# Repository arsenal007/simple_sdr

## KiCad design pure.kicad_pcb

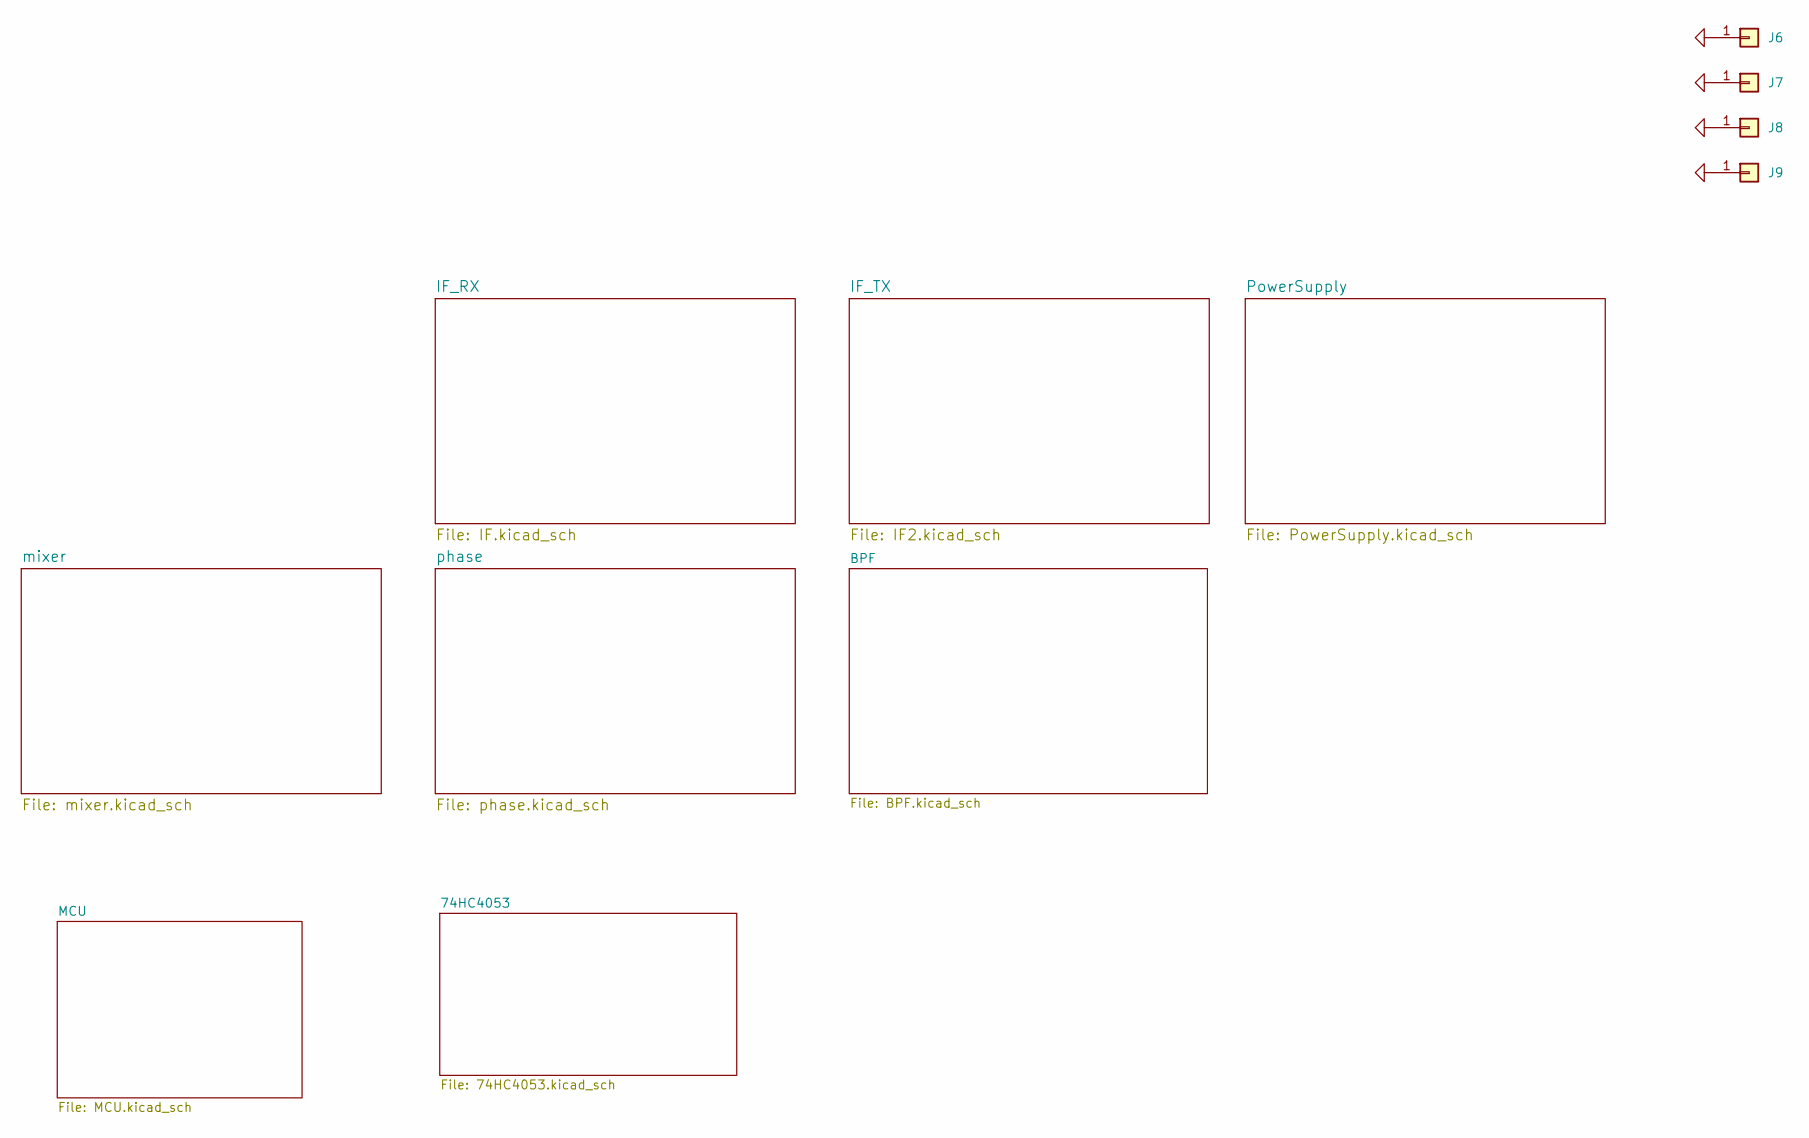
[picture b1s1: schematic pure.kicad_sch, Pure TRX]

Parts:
J6, J7, J8, J9: Conn_01x01; MountingHole_3.2mm_M3_DIN965_Pad

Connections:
GND: J6.1, J7.1, J8.1, J9.1; also elsewhere on the board

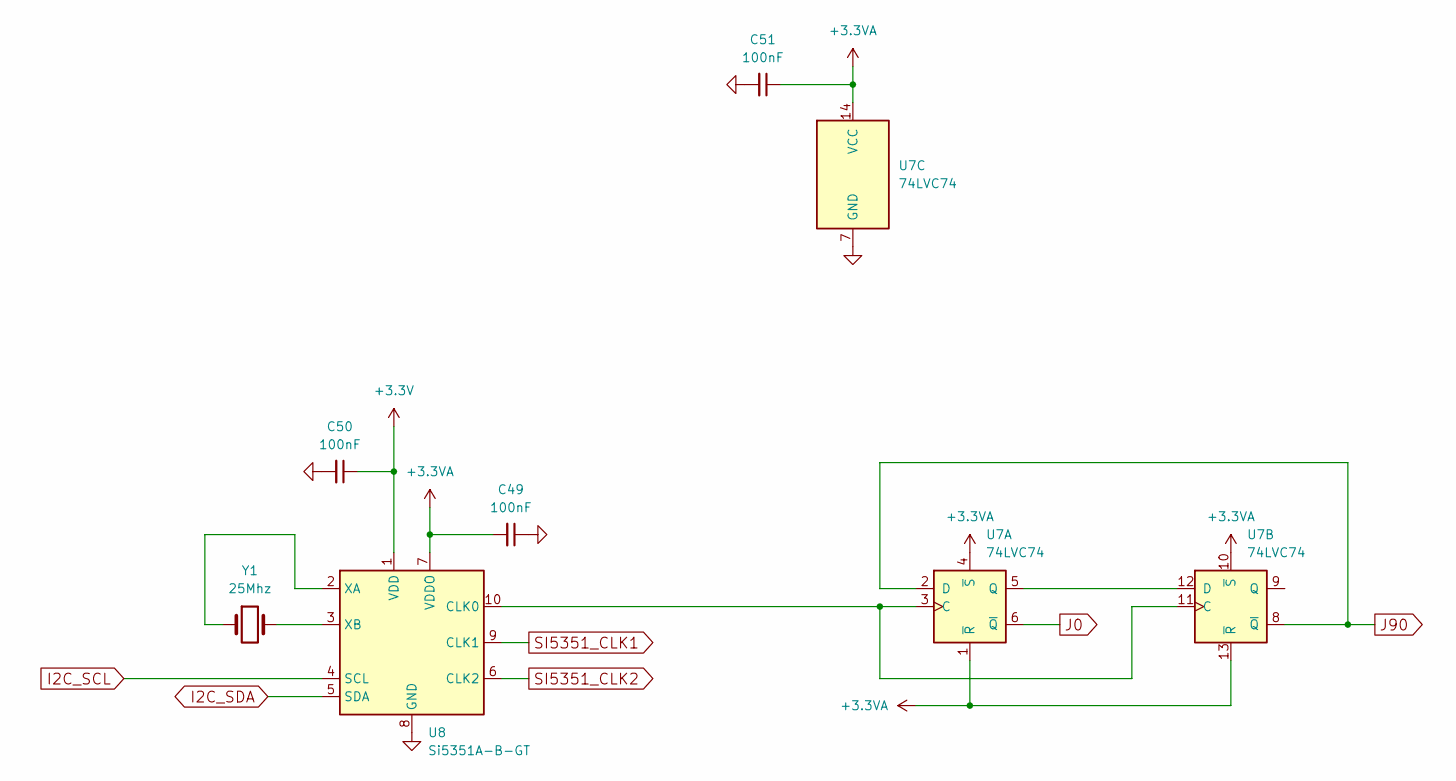
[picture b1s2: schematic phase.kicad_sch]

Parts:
C49, C50, C51: 100nF; C_1206_0603
U7: 74LVC74; TSSOP-14_4.4x5mm_P0.65mm
U8: Si5351A-B-GT; MSOP-10_3x3mm_P0.5mm
Y1: 25Mhz; Crystal_HC49-U_Vertical

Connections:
+3.3V: C50.1, U8.1 (VDD); also elsewhere on the board
+3.3VA: C49.2, C51.1, U7.1 (~R), U7.4 (~S), U7.10 (~S), U7.13 (~R), U7.14 (VCC), U8.7 (VDDO); also elsewhere on the board
GND: C49.1, C50.2, C51.2, U7.7 (GND), U8.8 (GND); also elsewhere on the board
I2C_SCL: U8.4 (SCL); also elsewhere on the board
I2C_SDA: U8.5 (SDA); also elsewhere on the board
J0: U7.6 (~Q); also elsewhere on the board
J90: U7.2 (D), U7.8 (~Q); also elsewhere on the board
unnamed: U7.3 (C), U7.11 (C), U8.10 (CLK0)
unnamed: U7.5 (Q), U7.12 (D)
unnamed: U8.2 (XA), Y1.1
unnamed: U8.3 (XB), Y1.2
SI5351_CLK1: U8.9 (CLK1)
SI5351_CLK2: U8.6 (CLK2)

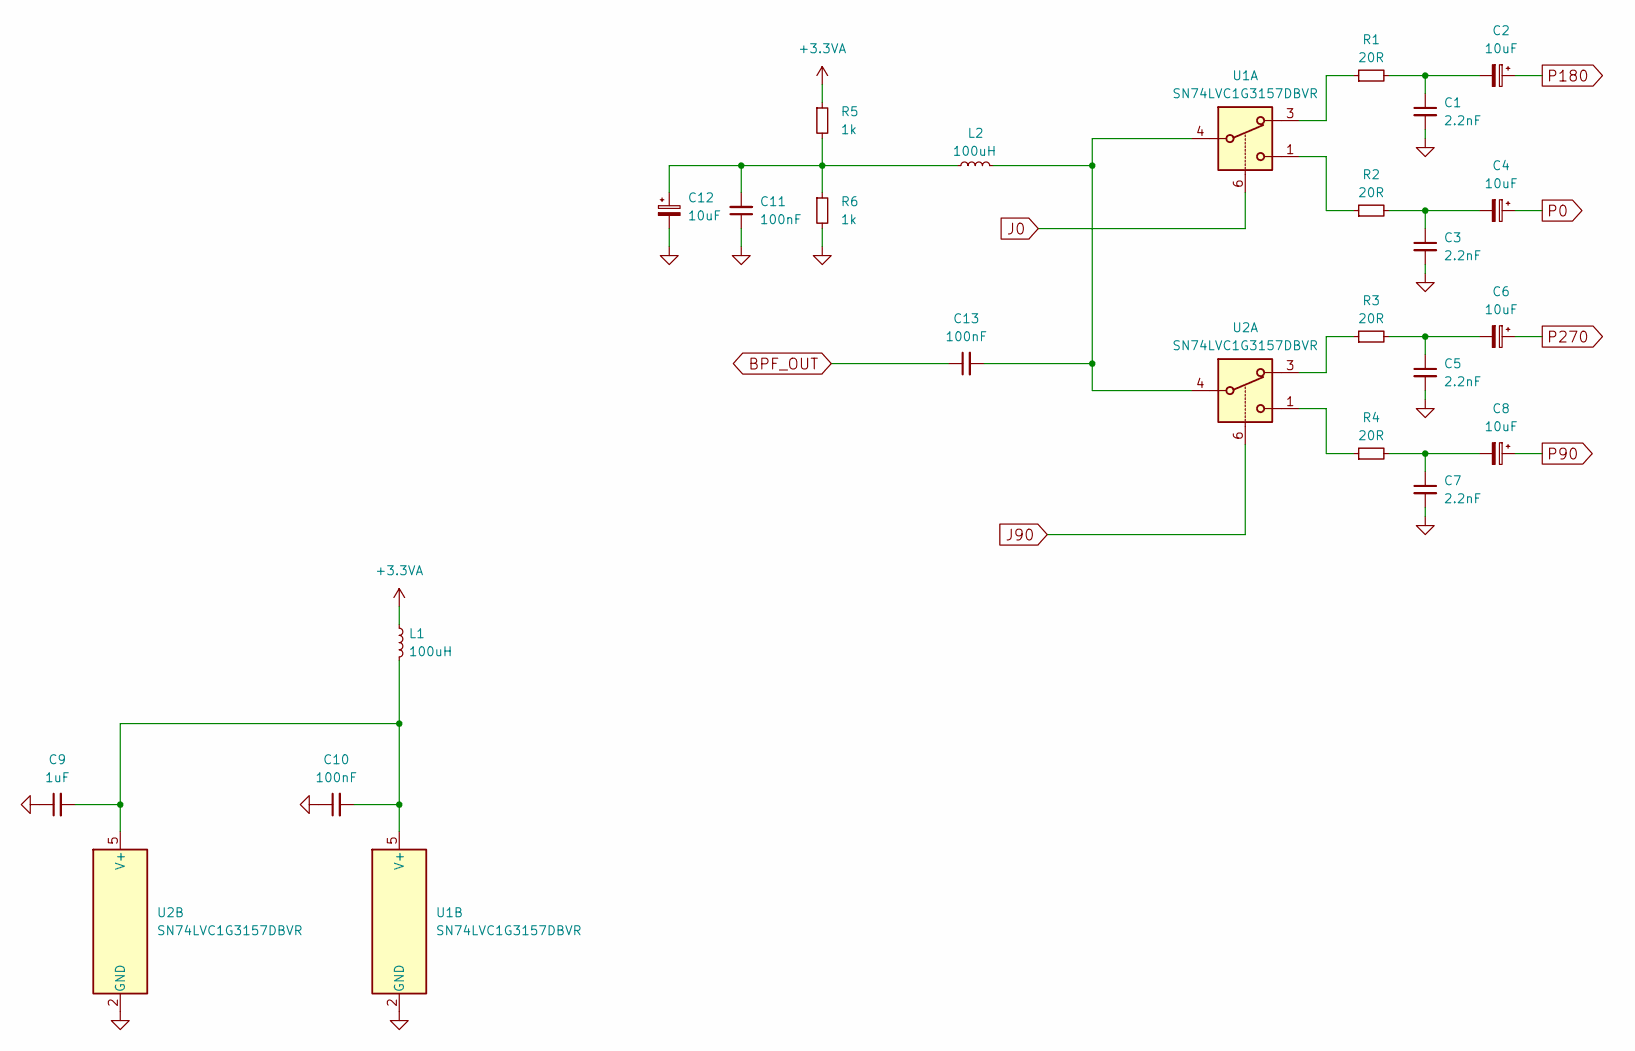
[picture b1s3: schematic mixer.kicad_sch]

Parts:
C1, C3, C5, C7: 2.2nF; C_1206_0603; JLCPCB C1604
C2, C4, C6, C8, C12: 10uF; CP_EIA-3216-18_Kemet-A_Pad1.58x1.35mm_HandSolder; JLCPCB C123294
C9: 1uF; C_0603_1608Metric_Pad1.08x0.95mm_HandSolder; JLCPCB C15849
C10, C11: 100nF; C_0603_1608Metric_Pad1.08x0.95mm_HandSolder; JLCPCB C14663
C13: 100nF; C_1206_0603; JLCPCB C14663
L1, L2: 100uH; L_Axial_L5.3mm_D2.2mm_P10.16mm_Horizontal_Vishay_IM-1; JLCPCB C394100
R1, R2, R3, R4: 20R; R_1206_0603; JLCPCB C22950
R5, R6: 1k; R_0603_1608Metric_Pad0.98x0.95mm_HandSolder; JLCPCB C21190
U1, U2: SN74LVC1G3157DBVR; SOT-23-6; JLCPCB C10426

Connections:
+3.3VA: L1.1, R5.1; also elsewhere on the board
BPF_OUT: C13.1; also elsewhere on the board
GND: C1.2, C3.2, C5.2, C7.2, C9.1, C10.1, C11.1, C12.2, R6.2, U1.2 (GND), U2.2 (GND); also elsewhere on the board
J0: U1.6; also elsewhere on the board
J90: U2.6; also elsewhere on the board
unnamed: C1.1, C2.2, R1.2
unnamed: C3.1, C4.2, R2.2
unnamed: C5.1, C6.2, R3.2
unnamed: C7.1, C8.2, R4.2
unnamed: C11.2, C12.1, L2.1, R5.2, R6.1
unnamed: C13.2, L2.2, U1.4, U2.4
unnamed: R1.1, U1.3
unnamed: R2.1, U1.1
unnamed: R3.1, U2.3
unnamed: R4.1, U2.1
unnamed: C9.2, C10.2, L1.2, U1.5 (V+), U2.5 (V+)
P0: C4.1; also elsewhere on the board
P90: C8.1; also elsewhere on the board
P180: C2.1; also elsewhere on the board
P270: C6.1; also elsewhere on the board

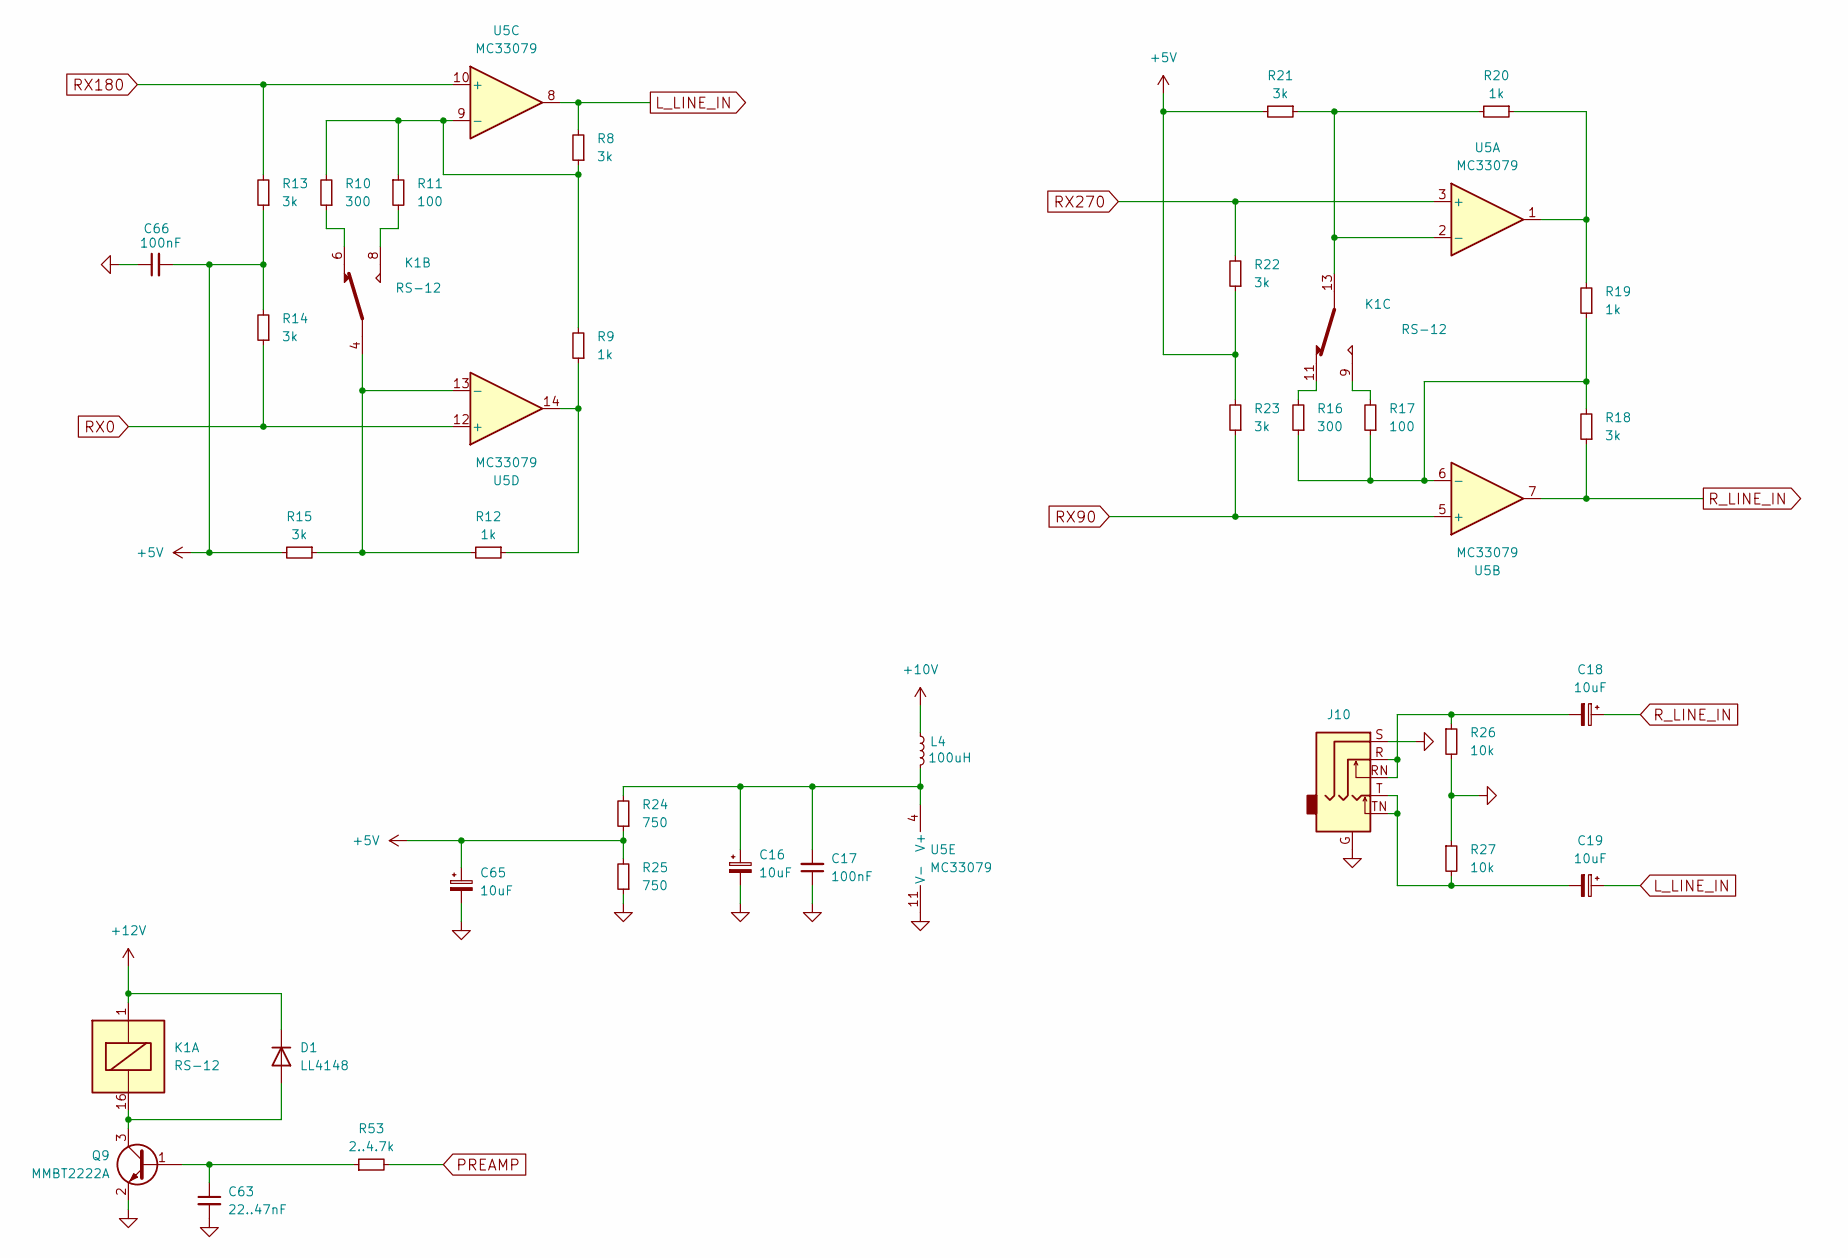
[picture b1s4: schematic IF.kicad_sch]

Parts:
C16, C18, C19, C65: 10uF; CP_EIA-3216-18_Kemet-A_Pad1.58x1.35mm_HandSolder; JLCPCB C123294
C17, C66: 100nF; C_1206_0603; JLCPCB C14663
C63: 22..47nF; C_1206_0603
D1: LL4148; D_MiniMELF
J10: AudioJack3_Ground_SwitchTR; Jack_3.5mm_CUI_SJ1-3525N_Horizontal
K1: RS-12; Relay_DPDT_Omron_G5V-2
L4: 100uH; L_1210_3225Metric_Pad1.42x2.65mm_HandSolder; JLCPCB C394100
Q9: MMBT2222A; SOT-23
R8, R13, R14, R15, R18, R21, R22, R23: 3k; R_0603_1608Metric_Pad0.98x0.95mm_HandSolder; JLCPCB C4211
R9, R12, R19, R20: 1k; R_0603_1608Metric_Pad0.98x0.95mm_HandSolder; JLCPCB C21190
R10, R16: 300; R_0603_1608Metric_Pad0.98x0.95mm_HandSolder; JLCPCB C23025
R11, R17: 100; R_0603_1608Metric_Pad0.98x0.95mm_HandSolder; JLCPCB C22775
R24, R25: 750; R_1206_0603; JLCPCB C23241
R26, R27: 10k; R_0603_1608Metric_Pad0.98x0.95mm_HandSolder; JLCPCB C25804
R53: 2..4.7k; R_1206_0603
U5: MC33079; SOIC-14_3.9x8.7mm_P1.27mm

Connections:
+5V: C65.1, C66.2, R13.1, R14.2, R15.2, R21.2, R22.1, R23.2, R24.1, R25.2; also elsewhere on the board
+10V: L4.1; also elsewhere on the board
+12V: D1.1 (K), K1.1; also elsewhere on the board
GND: C16.2, C17.1, C63.2, C65.2, C66.1, J10.G, J10.S, Q9.2 (E), R25.1, R26.2, R27.1, U5.11 (V-); also elsewhere on the board
L_LINE_IN: C19.1, R8.2, U5.8
unnamed: C18.2, J10.R, J10.RN, R26.1
unnamed: C19.2, J10.T, J10.TN, R27.2
unnamed: D1.2 (A), K1.16, Q9.3 (C)
unnamed: K1.6, R10.1
unnamed: K1.8, R11.2
unnamed: K1.9, R17.2
unnamed: K1.11, R16.2
unnamed: C63.1, Q9.1 (B), R53.1
unnamed: R9.1, R12.1, U5.14
unnamed: R19.2, R20.1, U5.1
unnamed: K1.13, R20.2, R21.1, U5.2 (-)
unnamed: R16.1, R17.1, R18.2, R19.1, U5.6 (-)
unnamed: R8.1, R9.2, R10.2, R11.1, U5.9 (-)
unnamed: K1.4, R12.2, R15.1, U5.13 (-)
unnamed: C16.1, C17.2, L4.2, R24.2, U5.4 (V+)
PREAMP: R53.2; also elsewhere on the board
RX0: R14.1, U5.12 (+); also elsewhere on the board
RX90: R23.1, U5.5 (+); also elsewhere on the board
RX180: R13.2, U5.10 (+); also elsewhere on the board
RX270: R22.2, U5.3 (+); also elsewhere on the board
R_LINE_IN: C18.1, R18.1, U5.7

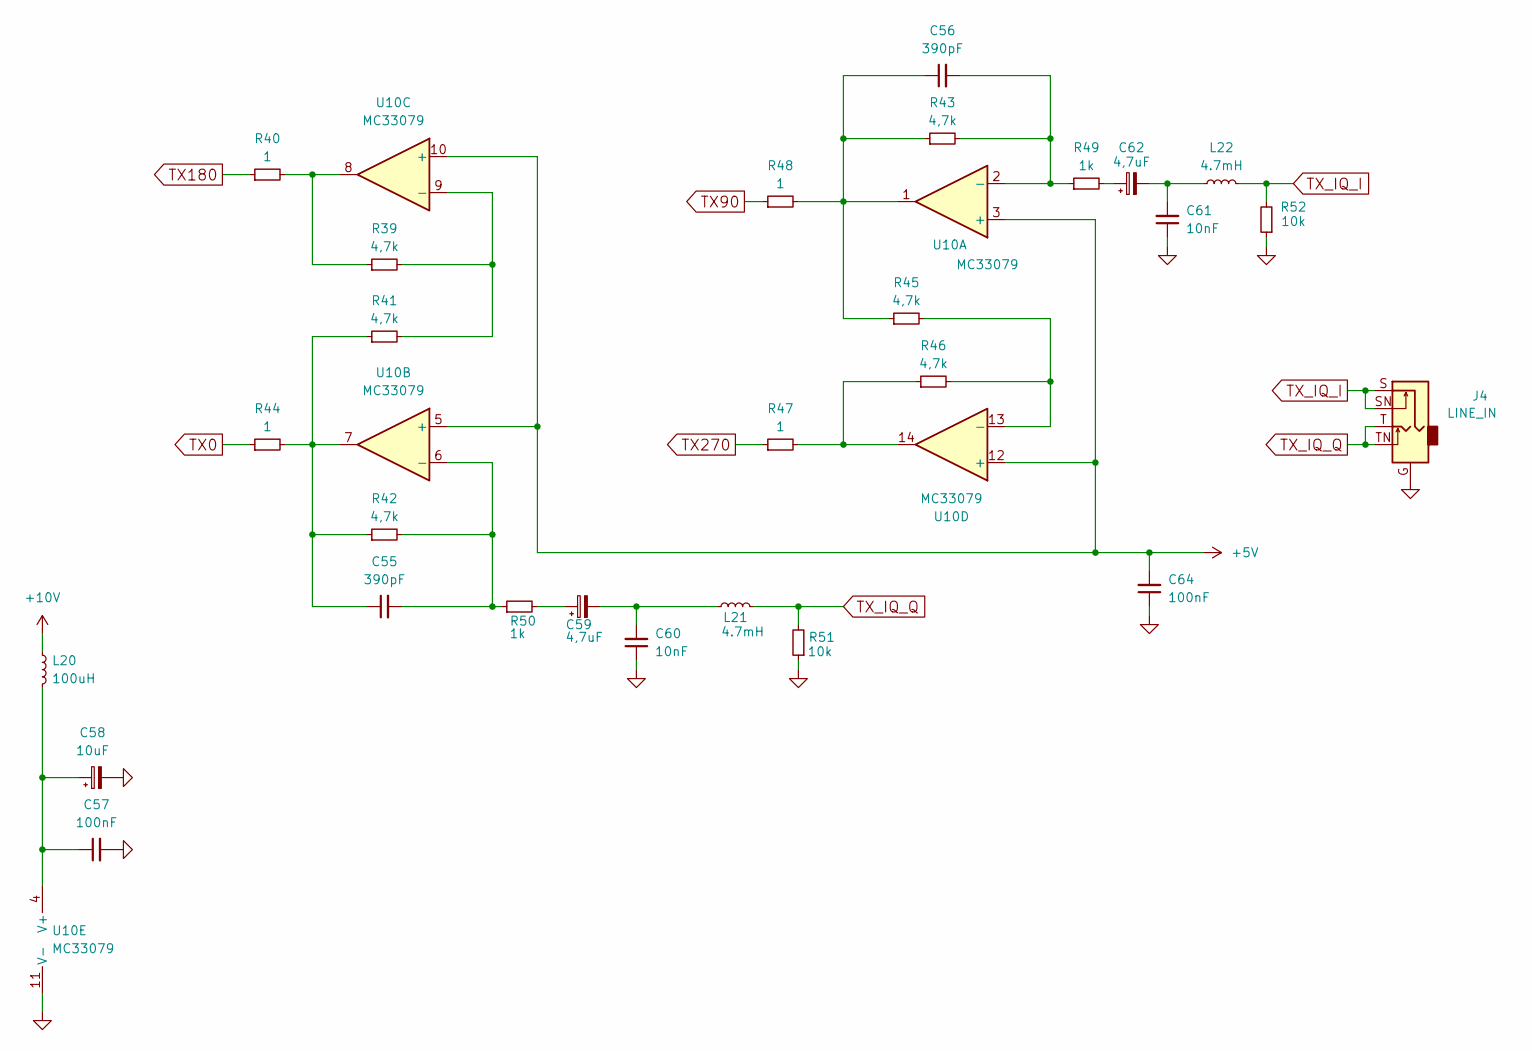
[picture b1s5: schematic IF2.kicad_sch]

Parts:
C55, C56: 390pF; C_0603_1608Metric_Pad1.08x0.95mm_HandSolder
C57: 100nF
C58: 10uF
C59, C62: 4,7uF
C60, C61: 10nF
C64: 100nF; C_1206_0603
J4: LINE_IN; Jack_3.5mm_CUI_SJ1-3525N_Horizontal
L20: 100uH
L21, L22: 4.7mH
R39, R41, R42, R43, R45, R46: 4,7k; R_0603_1608Metric_Pad0.98x0.95mm_HandSolder
R40, R44, R47, R48: 1; R_1206_0603
R49, R50: 1k; R_0603_1608Metric_Pad0.98x0.95mm_HandSolder
R51, R52: 10k
U10: MC33079; SOIC-14_3.9x8.7mm_P1.27mm

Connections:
+5V: C64.2, U10.3 (+), U10.5 (+), U10.10 (+), U10.12 (+); also elsewhere on the board
GND: C57.2, C58.2, C60.1, C61.1, C64.1, J4.G, R51.1, R52.1, U10.11 (V-); also elsewhere on the board
unnamed: C55.1, R41.1, R42.1, R44.2, U10.7
unnamed: C56.1, R43.1, R45.1, R48.2, U10.1
unnamed: C59.1, R50.2
unnamed: C59.2, C60.2, L21.1
unnamed: C61.2, C62.2, L22.1
unnamed: C62.1, R49.2
unnamed: R39.1, R40.2, U10.8
unnamed: R46.1, R47.2, U10.14
unnamed: C56.2, R43.2, R49.1, U10.2 (-)
unnamed: C55.2, R42.2, R50.1, U10.6 (-)
unnamed: R39.2, R41.2, U10.9 (-)
unnamed: R45.2, R46.2, U10.13 (-)
unnamed: C57.1, C58.1, L20.2, U10.4 (V+)
TX0: R44.1; also elsewhere on the board
TX90: R48.1; also elsewhere on the board
TX180: R40.1; also elsewhere on the board
TX270: R47.1; also elsewhere on the board
TX_IQ_I: J4.S, J4.SN, L22.2, R52.2
TX_IQ_Q: J4.T, J4.TN, L21.2, R51.2

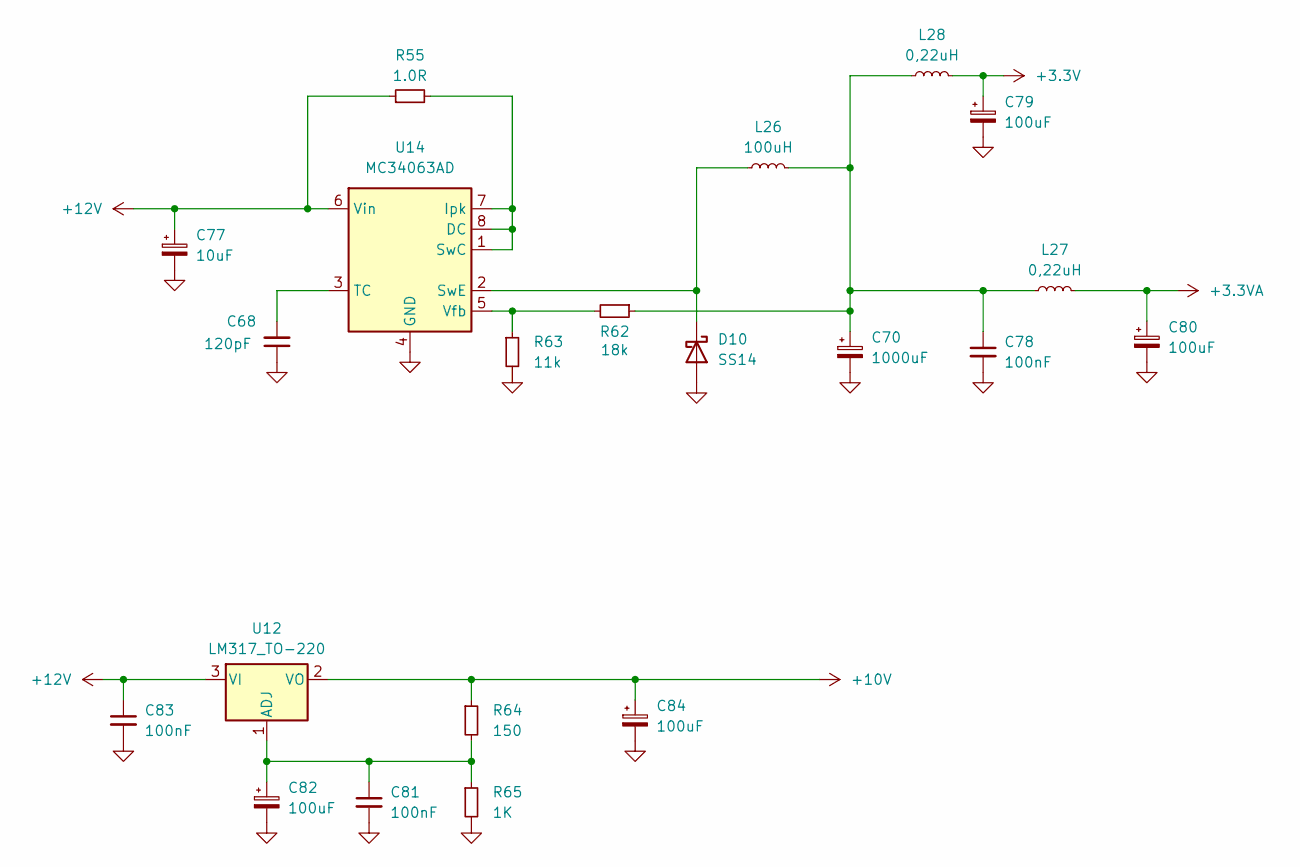
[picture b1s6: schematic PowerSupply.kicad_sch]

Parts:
C68: 120pF; C_0603_1608Metric_Pad1.08x0.95mm_HandSolder
C70: 1000uF
C77: 10uF; CP_Radial_D5.0mm_P2.00mm
C78, C81, C83: 100nF; C_1206_0603
C79, C80, C82, C84: 100uF; CP_Radial_D6.3mm_P2.50mm
D10: SS14; D_SMA
L26: 100uH
L27, L28: 0,22uH; R_Axial_DIN0207_L6.3mm_D2.5mm_P10.16mm_Horizontal
R55: 1.0R; R_1206_0603
R62: 18k; R_1206_0603
R63: 11k; R_1206_0603
R64: 150; R_1206_0603
R65: 1K; R_1206_0603
U12: LM317_TO-220; TO-220-3_Horizontal_TabDown
U14: MC34063AD; SOIC-8_3.9x4.9mm_P1.27mm

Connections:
+3.3V: C79.1, L28.2; also elsewhere on the board
+3.3VA: C80.1, L27.2; also elsewhere on the board
+10V: C84.1, R64.1, U12.2 (VO); also elsewhere on the board
+12V: C77.1, C83.1, R55.1, U12.3 (VI), U14.6 (Vin); also elsewhere on the board
GND: C68.1, C70.2, C77.2, C78.2, C79.2, C80.2, C81.2, C82.2, C83.2, C84.2, D10.2 (A), R63.2, R65.2, U14.4 (GND); also elsewhere on the board
unnamed: C70.1, C78.1, L26.2, L27.1, L28.1, R62.1
unnamed: D10.1 (K), L26.1, U14.2 (SwE)
unnamed: C81.1, C82.1, R64.2, R65.1, U12.1 (ADJ)
unnamed: R55.2, U14.1 (SwC), U14.7 (Ipk), U14.8 (DC)
unnamed: C68.2, U14.3 (TC)
unnamed: R62.2, R63.1, U14.5 (Vfb)

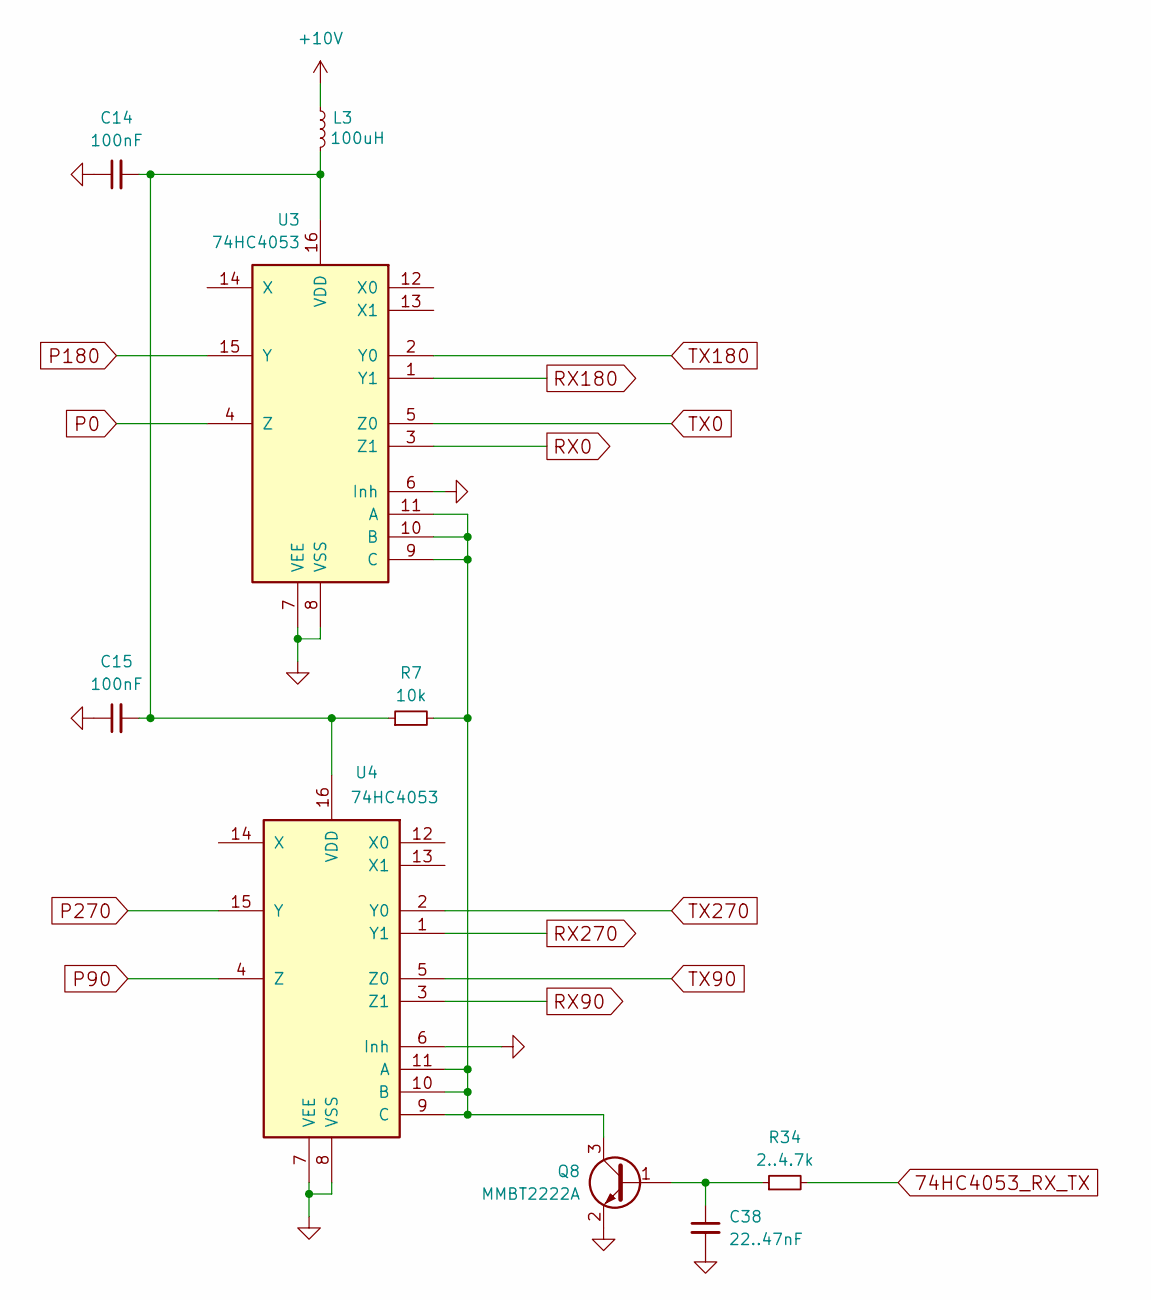
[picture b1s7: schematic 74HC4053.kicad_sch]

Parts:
C14, C15: 100nF; C_0603_1608Metric_Pad1.08x0.95mm_HandSolder; JLCPCB C14663
C38: 22..47nF
L3: 100uH; L_1210_3225Metric_Pad1.42x2.65mm_HandSolder; JLCPCB C394100
Q8: MMBT2222A; SOT-23
R7: 10k; R_0603_1608Metric_Pad0.98x0.95mm_HandSolder; JLCPCB C25804
R34: 2..4.7k
U3, U4: 74HC4053; SO-16_3.9x9.9mm_P1.27mm; JLCPCB C9386

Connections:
+10V: L3.1; also elsewhere on the board
GND: C14.1, C15.1, C38.2, Q8.2 (E), U3.6 (Inh), U3.7 (VEE), U3.8 (VSS), U4.6 (Inh), U4.7 (VEE), U4.8 (VSS); also elsewhere on the board
unnamed: C38.1, Q8.1 (B), R34.1
unnamed: Q8.3 (C), R7.2, U3.9 (C), U3.10 (B), U3.11 (A), U4.9 (C), U4.10 (B), U4.11 (A)
unnamed: C14.2, C15.2, L3.2, R7.1, U3.16 (VDD), U4.16 (VDD)
P0: U3.4 (Z); also elsewhere on the board
P90: U4.4 (Z); also elsewhere on the board
P180: U3.15 (Y); also elsewhere on the board
P270: U4.15 (Y); also elsewhere on the board
RX0: U3.3 (Z1); also elsewhere on the board
RX90: U4.3 (Z1); also elsewhere on the board
RX180: U3.1 (Y1); also elsewhere on the board
RX270: U4.1 (Y1); also elsewhere on the board
TX0: U3.5 (Z0); also elsewhere on the board
TX90: U4.5 (Z0); also elsewhere on the board
TX180: U3.2 (Y0); also elsewhere on the board
TX270: U4.2 (Y0); also elsewhere on the board

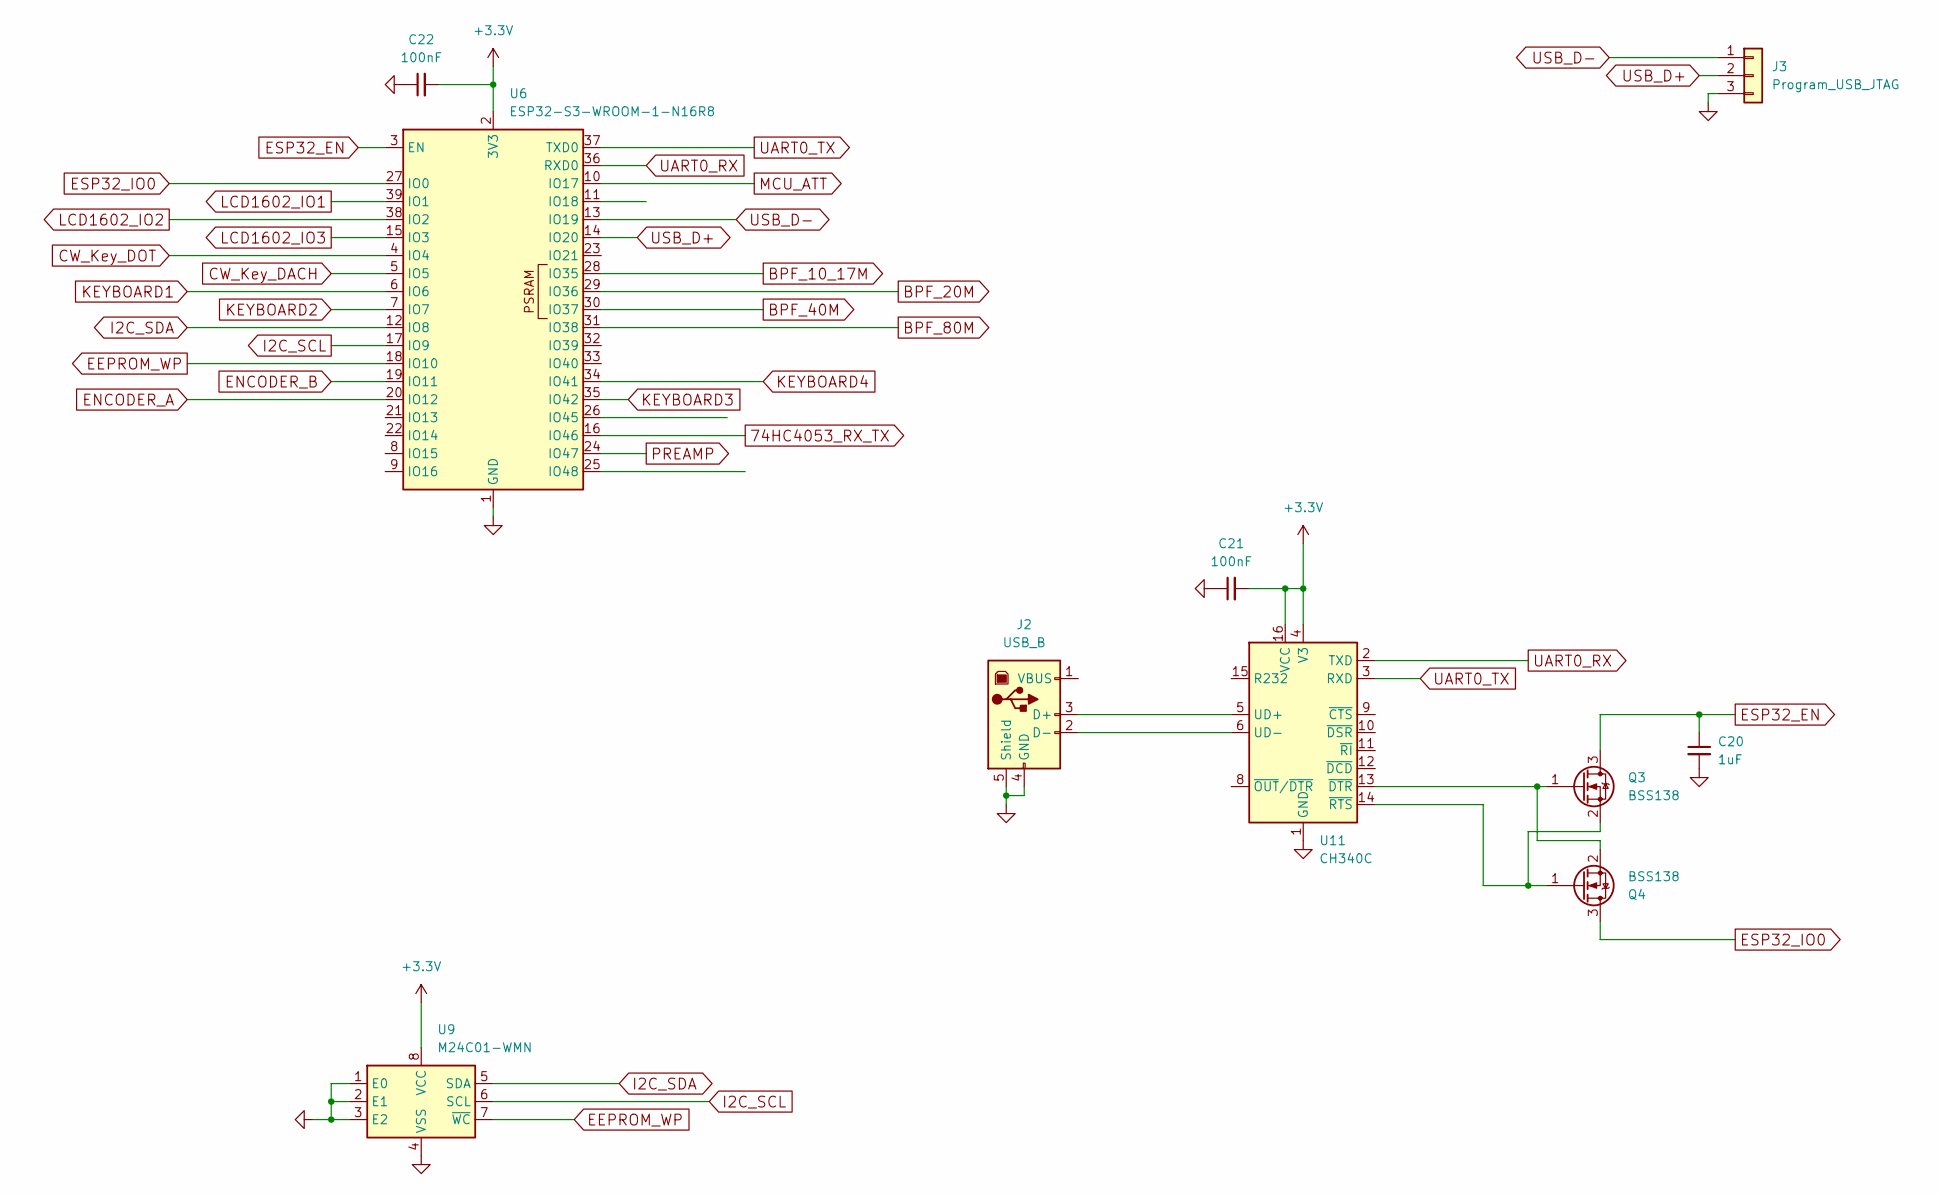
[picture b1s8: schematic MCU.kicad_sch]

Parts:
C20: 1uF; C_0603_1608Metric_Pad1.08x0.95mm_HandSolder; JLCPCB C15849
C21, C22: 100nF; C_0603_1608Metric_Pad1.08x0.95mm_HandSolder; JLCPCB C14663
J2: USB_B; USB_B_OST_USB-B1HSxx_Horizontal
J3: Program_USB_JTAG; PinHeader_1x03_P2.54mm_Vertical
Q3: BSS138; SOT-23; JLCPCB C82045
Q4: BSS138; SOT-23
U6: ESP32-S3-WROOM-1-N16R8; ESP32-S3-WROOM-1; JLCPCB C2913202
U9: M24C01-WMN; SOIC-8_3.9x4.9mm_P1.27mm
U11: CH340C; SOIC-16_3.9x9.9mm_P1.27mm; JLCPCB C7464026

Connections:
74HC4053_RX_TX: U6.16 (IO46)
+3.3V: C21.2, C22.2, U6.2 (3V3), U9.8 (VCC), U11.4 (V3), U11.16 (VCC); also elsewhere on the board
BPF_10_17M: U6.28 (IO35); also elsewhere on the board
BPF_20M: U6.29 (IO36); also elsewhere on the board
BPF_40M: U6.30 (IO37); also elsewhere on the board
BPF_80M: U6.31 (IO38); also elsewhere on the board
CW_Key_DACH: U6.5 (IO5)
CW_Key_DOT: U6.4 (IO4)
EEPROM_WP: U6.18 (IO10), U9.7 (~WC)
ENCODER_A: U6.20 (IO12)
ENCODER_B: U6.19 (IO11)
ESP32_EN: C20.1, Q3.3 (D), U6.3 (EN)
ESP32_IO0: Q4.3 (D), U6.27 (IO0)
GND: C20.2, C21.1, C22.1, J2.4 (GND), J2.5 (Shield), J3.3, U6.1 (GND), U6.40 (GND), U6.41 (GND), U9.1 (E0), U9.2 (E1), U9.3 (E2), U9.4 (VSS), U11.1 (GND); also elsewhere on the board
I2C_SCL: U6.17 (IO9), U9.6 (SCL); also elsewhere on the board
I2C_SDA: U6.12 (IO8), U9.5 (SDA); also elsewhere on the board
KEYBOARD1: U6.6 (IO6)
KEYBOARD2: U6.7 (IO7)
KEYBOARD3: U6.35 (IO42)
KEYBOARD4: U6.34 (IO41)
LCD1602_IO1: U6.39 (IO1)
LCD1602_IO2: U6.38 (IO2)
LCD1602_IO3: U6.15 (IO3)
MCU_ATT: U6.10 (IO17); also elsewhere on the board
unnamed: J2.3 (D+), U11.5 (UD+)
unnamed: J2.2 (D-), U11.6 (UD-)
unnamed: Q3.1 (G), Q4.2 (S), U11.13 (~DTR)
unnamed: Q3.2 (S), Q4.1 (G), U11.14 (~RTS)
PREAMP: U6.24 (IO47); also elsewhere on the board
UART0_RX: U6.36 (RXD0), U11.2 (TXD)
UART0_TX: U6.37 (TXD0), U11.3 (RXD)
USB_D+: J3.2, U6.14 (IO20)
USB_D-: J3.1, U6.13 (IO19)

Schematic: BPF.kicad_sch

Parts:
C52, C53: 100nF; C_1206_0603
C54: 10uF; CP_EIA-3216-18_Kemet-A_Pad1.58x1.35mm_HandSolder
L17: 10uH
L18, L19: 100uH; L_Axial_L5.3mm_D2.2mm_P10.16mm_Horizontal_Vishay_IM-1
R37, R38: 1k; R_0603_1608Metric_Pad0.98x0.95mm_HandSolder

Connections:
12v_BPF: C52.1, C53.1, C54.1, L17.2, L18.1, L19.1; also elsewhere on the board
BPF_IN: R38.2; also elsewhere on the board
BPF_OUT: R37.2; also elsewhere on the board
GND: C52.2, C53.2, C54.2; also elsewhere on the board
unnamed: L18.2, R37.1
unnamed: L19.2, R38.1

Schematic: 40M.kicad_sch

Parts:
C33: 360; C_0603_1608Metric_Pad1.08x0.95mm_HandSolder; JLCPCB C694496
C34: 390; C_0603_1608Metric_Pad1.08x0.95mm_HandSolder; JLCPCB C599667
C35: 100nF; C_1206_0603
C36: 360; C_1206_0603; JLCPCB C694496
C37: 22..47nF; C_1206_0603
C39: 470; C_0603_1608Metric_Pad1.08x0.95mm_HandSolder; JLCPCB C694496
C40: 470; C_1206_0603; JLCPCB C694496
D6, D7: BAP50-03; D_SOD-323_HandSoldering; JLCPCB C130411
L11, L13: 1uH; Resistor_SMD+THTuniversal_0603to2512_RM10_HandSoldering
L12: 2,2uH; Resistor_SMD+THTuniversal_0603to2512_RM10_HandSoldering
Q7: MMBT2222A; SOT-23
R32: 10k; R_0603_1608Metric_Pad0.98x0.95mm_HandSolder; JLCPCB C25804
R33: 2..4.7k; R_1206_0603

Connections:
12v_BPF: R32.1; also elsewhere on the board
BPF_40M: R33.2; also elsewhere on the board
BPF_IN: D6.2 (A); also elsewhere on the board
BPF_OUT: D7.2 (A); also elsewhere on the board
GND: C33.2, C35.2, C36.2, C37.2, C39.2, C40.2, Q7.2 (E); also elsewhere on the board
unnamed: C34.2, L12.1
unnamed: C33.1, C34.1, C39.1, D6.1 (K), L11.1
unnamed: C36.1, C40.1, D7.1 (K), L12.2, L13.1
unnamed: C37.1, Q7.1 (B), R33.1
unnamed: C35.1, L11.2, L13.2, Q7.3 (C), R32.2

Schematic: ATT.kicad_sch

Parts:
C67, C71: 100nF; C_1206_0603
C69: 22..47nF; C_1206_0603
C72: 120pF; C_0603_1608Metric_Pad1.08x0.95mm_HandSolder
C73: 220pF; C_1206_0603
C74: 120pF
C75, C76: 3,3nF; C_1206_0603
D11: LL4148; D_MiniMELF
J5: INPUT_OUTPUT; U.FL_Molex_MCRF_73412-0110_Vertical
K2: RS-12; Relay_DPDT_Omron_G5V-2
L23, L24: 0,22uH; Resistor_SMD+THTuniversal_0603to2512_RM10_HandSoldering
L25: 4,7uH; Resistor_SMD+THTuniversal_0603to2512_RM10_HandSoldering
Q2: MMBT2222A; SOT-23
R54: 2..4.7k; R_1206_0603
R56, R57, R58, R59, R60, R61: 1k; R_1206_0603

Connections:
+12V: D11.1 (K), K2.1; also elsewhere on the board
BPF_IN: C67.1; also elsewhere on the board
GND: C69.2, C72.1, C73.1, C74.1, J5.2 (Ext), L25.1, Q2.2 (E), R56.1, R58.1, R59.1, R61.1; also elsewhere on the board
MCU_ATT: R54.2; also elsewhere on the board
unnamed: C67.2, K2.13
unnamed: C71.1, C74.2, L23.2
unnamed: C71.2, K2.4
unnamed: C72.2, C75.1, L24.1
unnamed: C73.2, L23.1, L24.2
unnamed: C75.2, C76.1, L25.2
unnamed: D11.2 (A), K2.16, Q2.3 (C)
unnamed: C76.2, J5.1 (In)
unnamed: K2.8, R57.1, R58.2, R59.2, R60.1
unnamed: K2.9, R56.2, R57.2, R60.2, R61.2
unnamed: K2.6, K2.11
unnamed: C69.1, Q2.1 (B), R54.1

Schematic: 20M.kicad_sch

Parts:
C27, C29: 390; C_1206_0603; JLCPCB C694496
C28: 180; C_1206_0603; JLCPCB C599667
C30: 22..47nF; C_1206_0603
C31: 100nF; C_1206_0603
D4, D5: BAP50-03; D_SOD-323_HandSoldering; JLCPCB C130411
L8, L10: 0,47uH; Resistor_SMD+THTuniversal_0603to2512_RM10_HandSoldering
L9: 1uH; Resistor_SMD+THTuniversal_0603to2512_RM10_HandSoldering
Q5: MMBT2222A; SOT-23
R30: 10k; R_0603_1608Metric_Pad0.98x0.95mm_HandSolder; JLCPCB C25804
R31: 2..4.7k; R_1206_0603

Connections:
12v_BPF: R30.1; also elsewhere on the board
BPF_20M: R31.2; also elsewhere on the board
BPF_IN: D4.2 (A); also elsewhere on the board
BPF_OUT: D5.2 (A); also elsewhere on the board
GND: C27.2, C29.2, C30.2, C31.2, Q5.2 (E); also elsewhere on the board
unnamed: C28.2, L9.1
unnamed: C27.1, C28.1, D4.1 (K), L8.1
unnamed: C29.1, D5.1 (K), L9.2, L10.1
unnamed: C30.1, Q5.1 (B), R31.1
unnamed: C31.1, L8.2, L10.2, Q5.3 (C), R30.2

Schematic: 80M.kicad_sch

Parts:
C41, C45: 1nF; C_0603_1608Metric_Pad1.08x0.95mm_HandSolder; JLCPCB C694496
C42, C46: 560; C_0603_1608Metric_Pad1.08x0.95mm_HandSolder; JLCPCB C694496
C43: 120; C_0603_1608Metric_Pad1.08x0.95mm_HandSolder; JLCPCB C599667
C44: 100nF; C_1206_0603
C47: 22..47nF; C_1206_0603
C48: 560; C_0603_1608Metric_Pad1.08x0.95mm_HandSolder; JLCPCB C599667
D8, D9: BAP50-03; D_SOD-323_HandSoldering; JLCPCB C130411
L14, L16: 2,2uH; Resistor_SMD+THTuniversal_0603to2512_RM10_HandSoldering
L15: 4,7uH; Resistor_SMD+THTuniversal_0603to2512_RM10_HandSoldering
Q1: MMBT2222A; SOT-23
R35: 10k; R_0603_1608Metric_Pad0.98x0.95mm_HandSolder; JLCPCB C25804
R36: 2..4.7k; R_1206_0603

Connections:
12v_BPF: R35.1; also elsewhere on the board
BPF_80M: R36.2; also elsewhere on the board
BPF_IN: D8.2 (A); also elsewhere on the board
BPF_OUT: D9.2 (A); also elsewhere on the board
GND: C41.2, C42.2, C44.2, C45.2, C46.2, C47.2, Q1.2 (E); also elsewhere on the board
unnamed: C43.2, C48.2, L15.1
unnamed: C41.1, C42.1, C43.1, C48.1, D8.1 (K), L14.1
unnamed: C45.1, C46.1, D9.1 (K), L15.2, L16.1
unnamed: C47.1, Q1.1 (B), R36.1
unnamed: C44.1, L14.2, L16.2, Q1.3 (C), R35.2
